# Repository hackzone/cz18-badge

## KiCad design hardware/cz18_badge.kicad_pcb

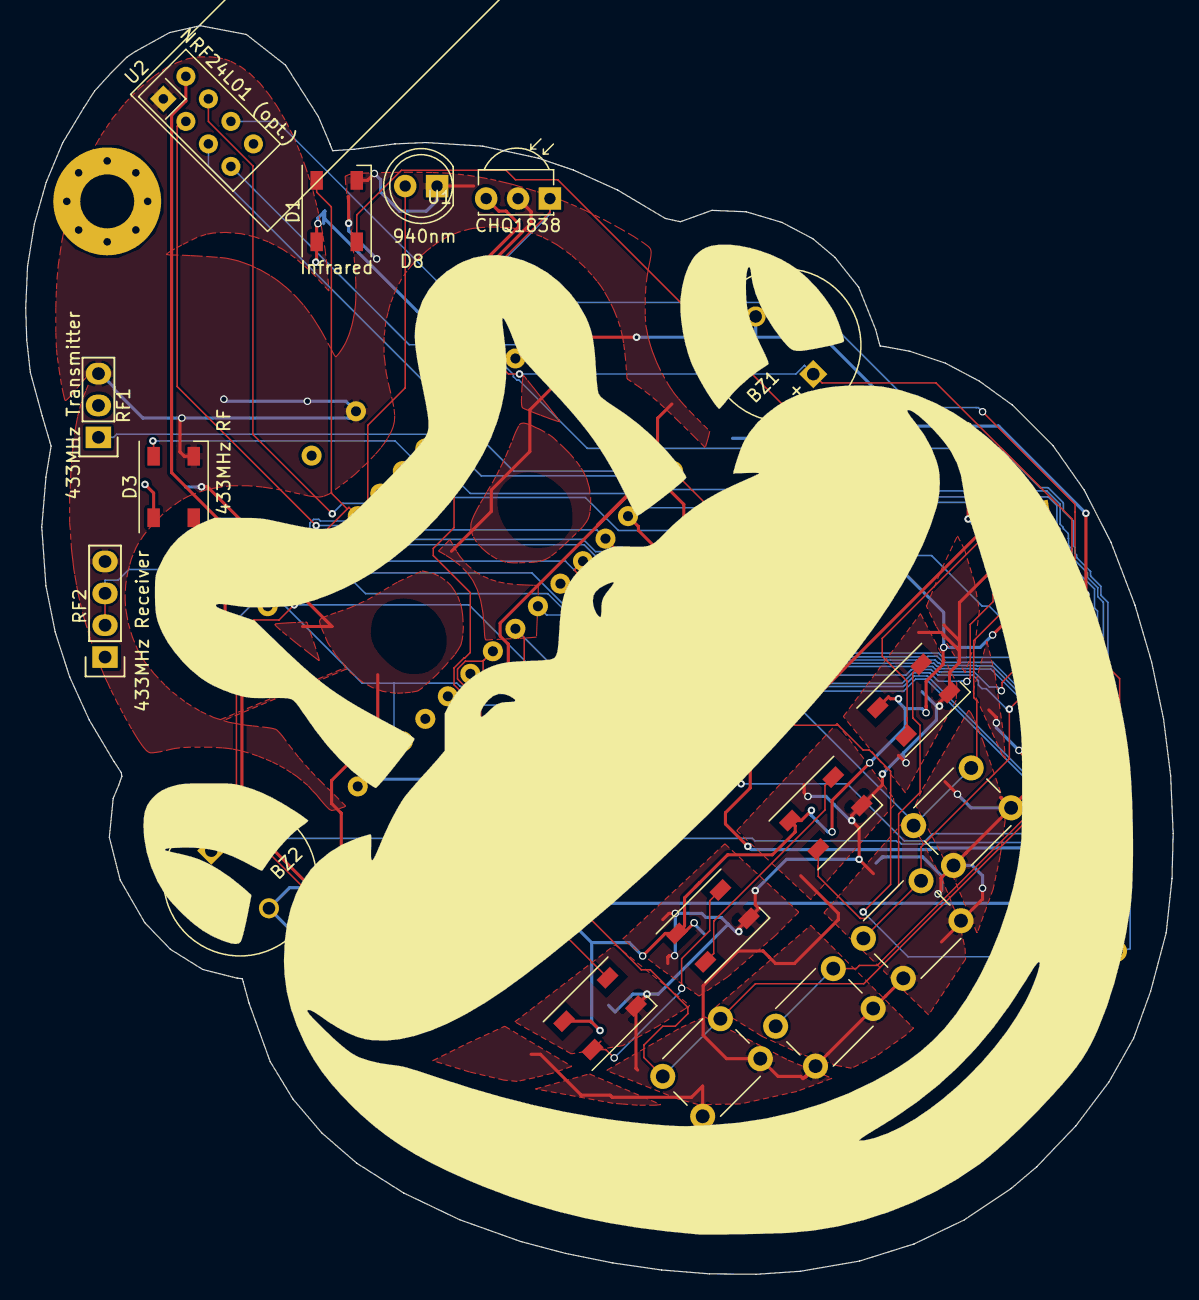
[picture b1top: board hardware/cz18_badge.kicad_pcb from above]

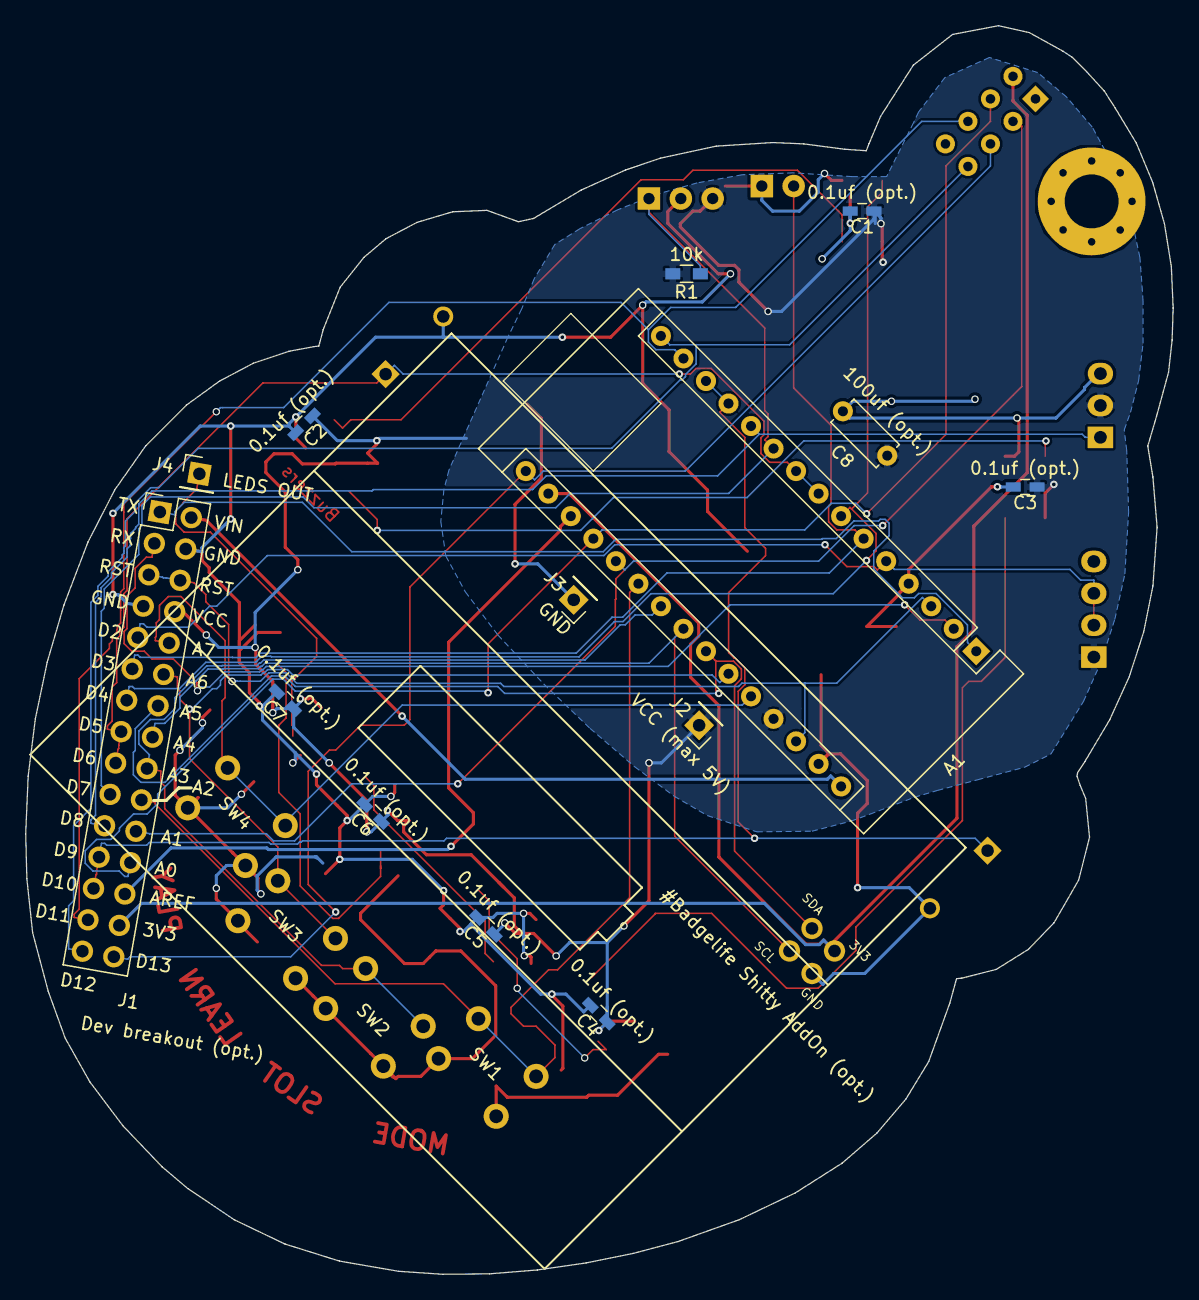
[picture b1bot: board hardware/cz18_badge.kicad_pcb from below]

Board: 2 copper layers, 91.5 x 99.6 mm, 36 parts (14 on the bottom side), 33 nets.

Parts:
A1: Arduino Nano v3.x; Arduino_Nano
BATT: AA Battery holder silkscreen; AA_Battery_holder_silkscreen
BZ1, BZ2: Buzzer; MagneticBuzzer_ProSignal_ABT-410-RC
C1, C2, C3, C4, C5, C6, C7: 0.1uf (opt.); C_0603_HandSoldering
C8: 100uf (opt.); C_Disc_D5.0mm_W2.5mm_P5.00mm
D1: Infrared; LED_SK6812_PLCC4_5.0x5.0mm_P3.2mm
D2, D4, D5, D6, D7: SK6812; LED_SK6812_PLCC4_5.0x5.0mm_P3.2mm
D3: 433MHz RF; LED_SK6812_PLCC4_5.0x5.0mm_P3.2mm
D8: 940nm; LED_D5.0mm
J1: Dev breakout (opt.); Pin_Header_Straight_2x15_Pitch2.54mm
J2: VCC (max 5V); Pin_Header_Straight_1x01_Pitch2.54mm
J3: GND; Pin_Header_Straight_1x01_Pitch2.54mm
J4: LEDS OUT; Pin_Header_Straight_1x01_Pitch2.54mm
R1: 10k; R_0603_HandSoldering
RF1: 433MHz Transmitter; RF_Transmitter_433_MHz
RF2: 433MHz Receiver; RF_Receiver_433_MHz
SILK: LOGO; Silkscreen
SW1: MODE; SW_PUSH_6mm_h4.3mm
SW2: SLOT; SW_PUSH_6mm_h4.3mm
SW3: LEARN; SW_PUSH_6mm_h4.3mm
SW4: PLAY; SW_PUSH_6mm_h4.3mm
TIN: LOGO; Tin
U1: CHQ1838; IRReceiver_Vishay_MOLD-3pin
U2: NRF24L01 (opt.); nRF24L01_Breakout
X1: #Badgelife Shitty AddOn (opt.); Badgelife-Shitty-2x2

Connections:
3V3: A1.17, J1.28, U2.2, X1.1
A0: A1.19, J1.24, U2.4
A1: A1.20, J1.22, U2.3
A2: A1.21, J1.20, SW1.1
A3: A1.22, J1.18, SW2.1
A4: A1.23, J1.16, X1.3
A5: A1.24, J1.14, X1.4
A6: A1.25, J1.12, SW3.1
A7: A1.26, J1.10, SW4.1
AREF: A1.18, J1.26
BUZZ1: A1.8, A1.9, BZ1.1, J1.15, J1.17
BUZZ2: A1.12, A1.13, BZ2.1, J1.23, J1.25
D2: A1.5, J1.9, RF2.2, RF2.3
D3: A1.6, D8.2, J1.11
D4: A1.7, D1.2, J1.13
D7: A1.10, J1.19, R1.1, U1.1
D8: A1.11, J1.21, RF1.1
D11: A1.14, J1.27, U2.6
D12: A1.15, J1.29, U2.7
D13: A1.16, J1.30, U2.5
GND: A1.4, A1.29, BZ1.2, BZ2.2, C1.2, C2.2, C3.2, C4.2, C5.2, C6.2, C7.2, C8.2, D1.1, D2.1, D3.1, D4.1, D5.1, D6.1, D7.1, D8.1, J1.4, J1.7, J3.1, RF1.3, RF2.4, SW1.2, SW2.2, SW3.2, SW4.2, U1.2, U2.1, X1.2
unnamed: D1.4, D2.2
unnamed: D2.4, D3.2
unnamed: D3.4, D4.2
unnamed: D4.4, D5.2
unnamed: D5.4, D6.2
unnamed: D6.4, D7.2
unnamed: D7.4, J4.1
RESET: A1.3, A1.28, J1.5, J1.6
RX: A1.2, J1.3
TX: A1.1, J1.1
VCC: A1.27, C1.1, C2.1, C3.1, C4.1, C5.1, C6.1, C7.1, C8.1, D1.3, D2.3, D3.3, D4.3, D5.3, D6.3, D7.3, J1.8, J2.1, R1.2, RF1.2, RF2.1, U1.3
VIN: A1.30, J1.2

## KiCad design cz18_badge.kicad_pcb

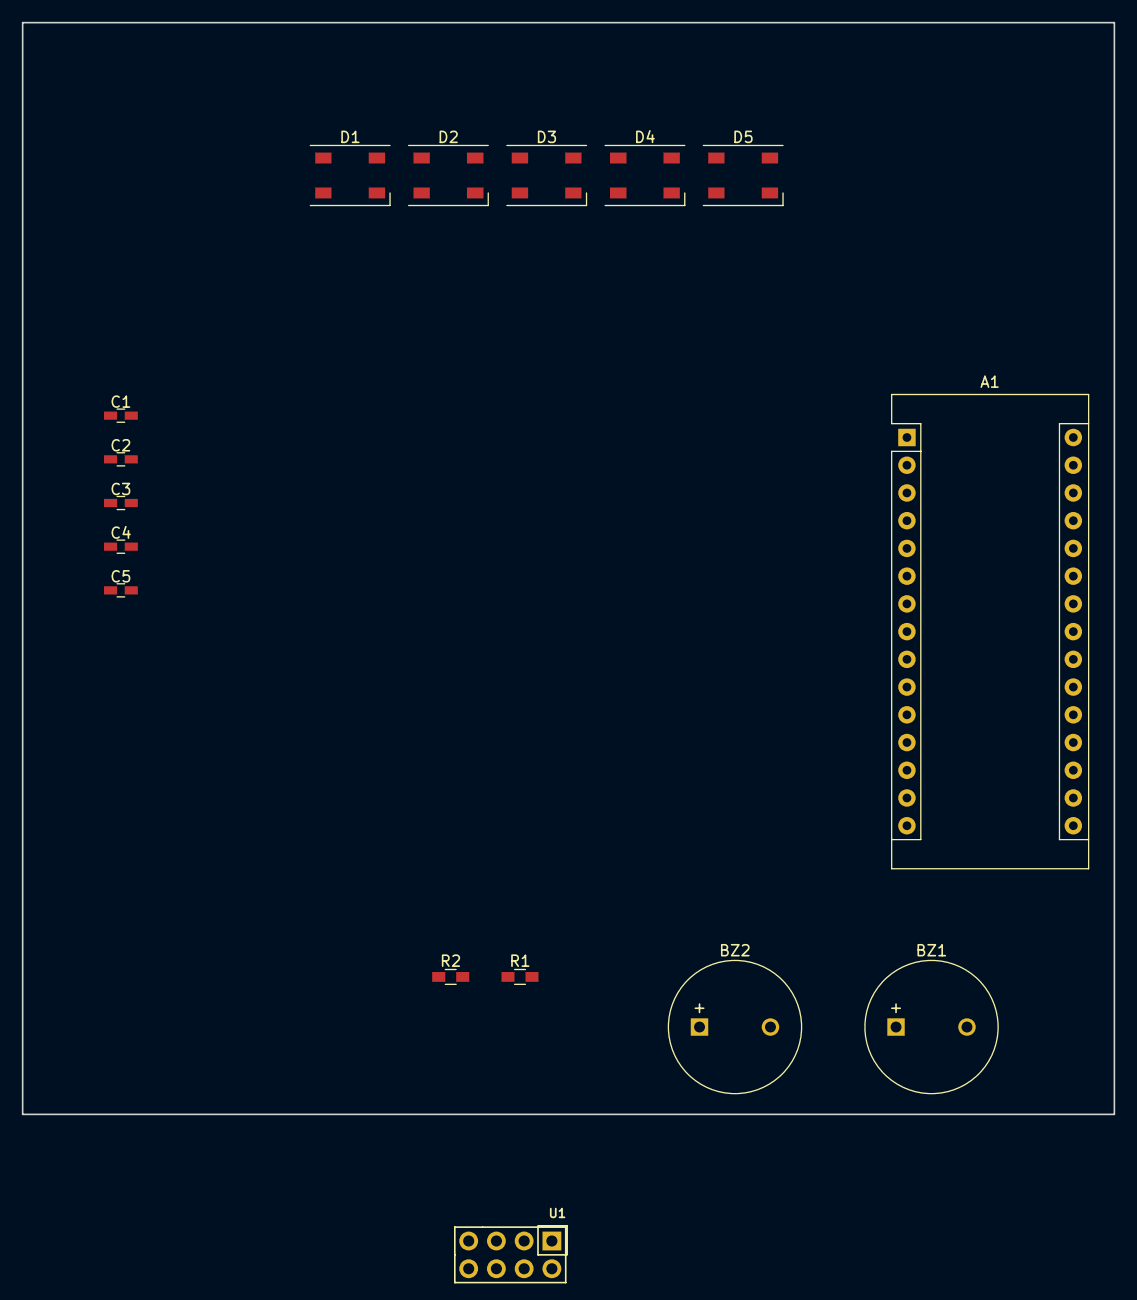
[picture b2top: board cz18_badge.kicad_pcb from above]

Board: 2 copper layers, 100.0 x 100.0 mm, 16 parts (0 on the bottom side), 10 nets, no tracks yet.

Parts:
A1: Arduino_Nano_v3.x; Arduino_Nano
BZ1, BZ2: Buzzer; MagneticBuzzer_ProSignal_ABT-410-RC
C1, C2, C3, C4, C5: 104; C_0603_HandSoldering
D1, D2, D3, D4, D5: SK6812; LED_SK6812_PLCC4_5.0x5.0mm_P3.2mm
R1, R2: 0k; R_0603_HandSoldering
U1: NRF24L01_Breakout; NRF24L01

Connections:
BUZZ1: A1.12, BZ1.1
BUZZ2: A1.13, BZ2.1
GNDREF: A1.4, A1.29, BZ1.2, BZ2.2, C1.2, C2.2, C3.2, C4.2, C5.2, D1.1, D2.1, D3.1, D4.1, D5.1, U1.1
unnamed: A1.27, R2.2
unnamed: A1.30, R1.2
unnamed: D1.4, D2.2
unnamed: D2.4, D3.2
unnamed: D3.4, D4.2
unnamed: D4.4, D5.2
VCC: C1.1, C2.1, C3.1, C4.1, C5.1, D1.3, D2.3, D3.3, D4.3, D5.3, R1.1, R2.1, U1.2

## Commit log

2018-05-21 Initial fill w/ portion of components populated
2018-05-21 Added non-standard libraries and modules
2018-05-21 Added todo comments
2018-06-03 Combined hardware and firmware into one repo
2018-06-03 Added firmware folder
2018-06-03 Initial library test
2018-06-03 Added library paths
2018-06-03 Added 433MHz modules
2018-06-04 Connected component labels
2018-06-04 Added battery and dev breakout, routed dev traces on test PCB
2018-06-04 Updated test PCB (single layer)
2018-06-09 WIP audio
2018-06-09 Not functional yet
2018-06-09 Finished Donkey Kong badge design
2018-06-09 Corrected donkey kong bitmaps, and added a fat (stretched) design alternative that provides more real estate
2018-06-10 Added buttons and 2 additional LEDs
2018-06-10 Added vector-kong drawings
2018-06-10 Implemented vectorised kong. All works, but no clearance between traces and areas. Will add manual fill zones.
2018-06-11 Added AA battery holder mod fiel to vector-kong directory
2018-06-11 Added preliminary gerbers
2018-06-11 Added Copper Eges svd and dxf.
2018-06-11 Moved battery holder file, added Defcon Shitty AddOn files
2018-06-11 Added Defcon Shitty AddOn footprint to pcb
2018-06-11 Added back hair
2018-06-11 Improved PCB annotation, working on manual fill zone colouring
2018-06-12 Minor fixes
2018-06-12 Added SVG and DXF files for the back hair.
2018-06-14 Added lanyard hole, annotated dev headers, moved components
2018-06-15 Finished annotation
2018-06-15 Added minimal track widths and clearances for JLCPCB
2018-06-15 Performed Autoroute, still 14 connections missing.
2018-06-15 Completed final manual routing
2018-06-15 Added eye shade fill zones again, and performed final modifications to tracks. Generated gerber files.
2018-06-15 PDFs of board layout
2018-06-17 Include the pin layout according to the wiring schematics
2018-06-17 Boilerplate for button debouncing and processing. Move the previous version into firmware.ino.old
2018-06-17 Tweak the debouncing interval and refactor button reading
2018-06-17 Swapped buttons to GND so we can use built-in atmega pullup resistors
2018-06-17 Correct pin layout
2018-06-20 Corrected folder structure
2018-06-20 added included library bounce2 to repos
2018-06-24 initial hookup of rcswitch and interface for RF module
2018-06-24 oopsie, forgot a change
2018-06-25 Refactor the button handling logic into a separate class
2018-06-26 Optimised SoftSynth interrupt routine to 385 cycles per channel
2018-07-03 Fixed IR receiver pinout not matching CHQ1838
2018-07-06 WIP: Add data loading from EEPROM
2018-07-14 Added CMake configs
2018-07-14 Cleaned up & implemented mode and slot selection. Buttons don't seem functional yet on this branch
2018-07-15 Fixed namespace
2018-07-15 Fixed the issue with jittering and unstable buttons
2018-07-15 rfmodule files
2018-07-15 update sketch
2018-07-15 fixed switches, added RFModule code
2018-07-15 Initial work on the IR learn and play and EEPROM rework
2018-07-15 recommit
2018-07-15 IR learn and play and eeprom fixes
2018-07-15 Fix the IR learn and play
2018-07-16 Add heurestic for determining whether the buttons on A6 and A7 are pressed
2018-07-22 Revert "recommit"
    This reverts commit 5d168a69e120a2ad2721263858ad8e2cba4bb2e5.
2018-07-22 Correct the firmware
2018-07-22 Refactor the button handling classes and remove unnecessary fields
2018-07-22 Rework learn and play for IR so that the UI is clearer
2018-07-22 Utilize IR slot only when it is used and add more delay to the `analogRead` switching
2018-07-28 l8est & gr8est
2018-07-28 Removed Tone lib
2018-07-28 Fixed notes
2018-07-29 Added cybers
2018-07-30 Added torchlight functionality as additional "module"
2018-07-30 Set RF module as startup again
2018-07-30 Fixed learning and playing targeting the wrong modules
2018-07-30 Stop the tunes when the notes are done playing
2018-07-30 Make sure that the routines match up with module count
2018-07-30 Do not attempt to use an RF slot if it was not already set to used
2018-08-03 Fixed left speaker output
2018-08-04 go-Disco!
